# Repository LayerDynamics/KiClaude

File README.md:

# kiclaude

**Claude Code, but for circuit boards.**

kiclaude is a browser-native, AI-native, KiCad-compatible EDA suite. You open a
`.kicad_pro` project in a browser tab, chat with Claude in the sidebar, and
every action — *"add a USB-C PD trigger for 9 V, with proper decoupling and a
fuse"*, *"route the high-speed pairs first, then power"*, *"is this board ready
to fab?"* — becomes a typed tool call that round-trips back to real
`.kicad_sch` / `.kicad_pcb` files on disk. Diffable. Reviewable. Yours.

Every chat lives next to a fully-featured visual editor: selection, drag,
multi-layer routing, zone fills, DRC overlays. Claude is a first-class
collaborator, not a chrome strip glued onto someone else's UI.

---

## Why this exists

Designing a PCB today forces a hard choice:

- **KiCad** is open and file-clean, but every action is manual. AI plugins are
  second-class citizens.
- **Flux / cloud EDA** has the AI, but your files live in a vendor cloud and you
  pay rent on your own designs.
- **tscircuit** is text-first (great for AI), but you lose the visual review
  that humans actually need.

kiclaude lives in the empty quadrant: **browser-native, open file format,
AI-native, local-first.** The files stay on your disk. The AI ships in the box.
The visual editor is real. None of those are bolted on.

## What's in the box

- **A real KiCad-format engine**, in Rust + WASM — schematic parser, PCB
  parser, deterministic emitter (round-trip-or-die, gated in CI), KCIR
  canonical intermediate representation, geometry kernel, R-tree index, DRC.
- **A typed MCP tool catalog** (`kc_*` for Claude, `ui_*` for the editor) so
  every edit is auditable and gated. Claude doesn't get raw `Write` access to
  your `.kicad_pcb` — it gets `kc_footprint_place_hint("near MCU, south edge")`
  and the placer resolves it.
- **A persistent chat sidebar** powered by the Claude Agent SDK, with session
  resume, hook-gated approvals, and a journal of every tool call (with revert).
- **The same `.claude/` artifacts work everywhere.** Slash commands like
  `/add-mcu esp32-s3`, `/pcb-review`, `/diffpair`, `/route-power`, `/bom-price`,
  `/pcb-fab` run from the in-app sidebar **and** from Claude Code on the CLI.
- **Headless `kiclaude` CLI** so anything Claude can do, CI can do.
- **A three.js board viewer** (`kithree`) for the 3D crowd.
- **An optional local daemon** (`kiconnector`) so Firefox and Safari users get
  filesystem access without waiting for FSA parity.

## Eight rules we won't break

1. The **KiCad file format** is the contract. Round-trip fidelity is a CI gate.
2. The **KCIR** is the in-memory contract — Rust-defined, TS + JSON Schema
   mirrors generated from it.
3. Claude operates through **typed tools, never free-form file edits**.
4. Claude reasons in **declarative hints**; raw coordinates are UI-only.
5. **Every MPN must resolve** against a real distributor. No hallucinated parts.
6. MCP tools are **stateless**. State lives in files.
7. **No prose from MCP tools** — structured JSON only; Claude narrates on top.
8. **Local-first, cloud-optional.** Anthropic API key is the only network
   dependency, and that's opt-in at first run.

If a future PR violates one of these, that's the PR that needs to lose. Not the
rule.

## Architecture, at a squint

```
                +-------------------------------+
                |  client/  (React + Vite +     |
                |  Radix + Tailwind + Zustand)  |
                |  kicanvas + kithree viewports |
                +---------------+---------------+
                                | WebSocket + REST :8080
                +---------------v---------------+
                |  services/server  (Hono GW)   |
                +---+-----------+-----------+---+
                    |           |           |
            :8082   |   :8083   |   :8084   |
       +------------v+ +--------v---+ +-----v----------+
       |   agent     | |  kiserver  | |  kiconnector   |
       | (Claude SDK)| | (PyO3 + ki)| | (kicad-cli)    |
       +------+------+ +-----+------+ +----------------+
              |              |
              | in-process MCP (kc_* tools)
              v              v
       +------------------------------+
       |  services/mcp                |
       |  + crates/ki  (KCIR, format) |
       |  + crates/cad (geom, DRC)    |
       +------------------------------+
                       ^
                       |  round-trip
                       v
              .kicad_pro / .kicad_sch / .kicad_pcb
```

| Path | What lives there |
|---|---|
| `crates/ki/` | KCIR types, S-expression lexer/parser, KiCad 9 emitter, PyO3 + wasm bindings |
| `crates/cad/` | Geometry, R-tree index, DRC kernel, length-match, impedance solver, 3D scene |
| `services/agent/` | FastAPI driver around the Claude Agent SDK (`:8082`) |
| `services/mcp/` | In-process MCP server with all `kc_*` and `ui_*` tools |
| `services/kiserver/` | FastAPI surface around the PyO3-loaded `ki_native` (`:8083`) |
| `services/kiconnector/` | Local broker for `kicad-cli` + Freerouting (`:8084`) |
| `services/server/` | Hono WebSocket + REST gateway (`:8080`) |
| `client/` | The browser editor (React 19, Vite, Tailwind, Zustand) |
| `packages/cli/` | The `kiclaude` Node CLI |
| `packages/kithree/` | three.js board viewer |
| `examples/blinky/` | Reference project the round-trip CI runs against |

## Quick start

```bash
# Rust
cargo test --workspace
cargo clippy --workspace --all-targets -- -D warnings

# Wasm bindings (consumed by client/)
wasm-pack build --target web crates/ki
wasm-pack build --target web crates/cad

# Python services
uv sync --all-extras
uv run pytest

# Node side
pnpm install
pnpm -r typecheck
pnpm -F client dev          # browser editor on http://localhost:5173

# CLI
pnpm -F @kiclaude/cli build
kiclaude --version
kiclaude mcp stdio          # talk to the MCP server from any MCP-capable host
kiclaude validate examples/blinky
```

For end-to-end Playwright smoke (gated on `ANTHROPIC_API_KEY`):

```bash
pnpm -F e2e test
```

## A taste of the slash commands

These ship in `.claude/commands/` and work both in-app and in Claude Code:

| Command | What it does |
|---|---|
| `/add-mcu esp32-s3` | Adds an MCU + USB + LDO + decoupling, ERC-clean |
| `/add-power buck-3v3-from-vbus` | Drops in a complete power subsystem |
| `/add-decoupling` | Audits every IC for missing bypass caps, proposes one per pin |
| `/diffpair` | Declares a diff pair, solves for impedance, routes it |
| `/route-power` | Routes power nets at net-class width with per-net approvals |
| `/route-signals` | Walk-around routes signal nets in dependency order |
| `/length-match` | Analyses declared length-match groups, queues serpentine tuning |
| `/explore-placements` | Spawns a sub-agent that tries N placements, ranks by track length × clearance headroom |
| `/erc-fix` / `/drc-fix` | Reads the highest-severity issue, proposes one fix, applies on approval, loops |
| `/pcb-review` | Full M3 design review: stackup, net classes, diff pairs, length match, decoupling, DRC |
| `/pcb-fab` | DFM dry-run, then full fab bundle (gerbers + drill + P&P + BOM) |
| `/bom-price` | Fan-out across Octopart / Mouser / Digi-Key / JLCPCB, returns cheapest mix |

## Status

We're tracking the [`M0–M3` plan](docs/plans/2026-05-21-kiclaude-m0-m3.md) —
139 of 146 tasks done as of this writing. The remaining set is the push-and-shove
router (the bottleneck), three live-distributor adapters, and a couple of UI gestures.
The full spec lives at [`docs/specs/SPEC-01-kiclaude.md`](docs/specs/SPEC-01-kiclaude.md);
if it disagrees with this README, the spec wins.

## License

Apache-2.0. The Freerouting integration runs as a separately-installed
subprocess so the GPL doesn't bleed into the rest of the tree
(see `NFR-009` in the spec, and `scripts/license_audit.sh` in CI).

## Contributing

The bar:

- `cargo test --workspace` is green
- `uv run pytest` is green
- `pnpm -r typecheck && pnpm -r test` are green
- Golden round-trip (`tests/golden/`) is green — if it isn't, the file emitter
  is wrong, even if KiCad opens the output
- New MCP tools land in the typed registry with input/output schemas and a
  note on whether they're Claude-facing (declarative) or UI-only (coordinate)

Open an issue, open a PR, or — easiest of all — open the project in the
browser and ask Claude to do it.

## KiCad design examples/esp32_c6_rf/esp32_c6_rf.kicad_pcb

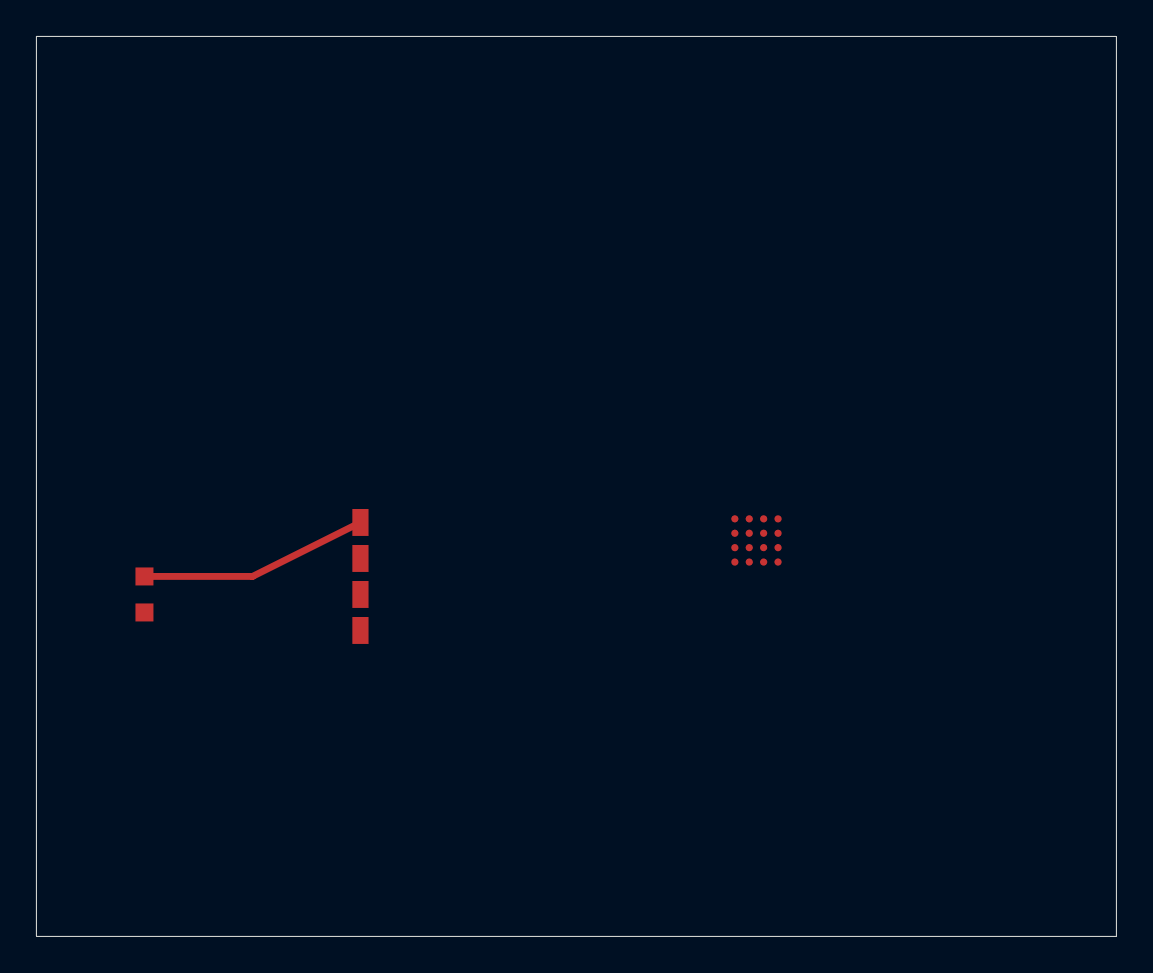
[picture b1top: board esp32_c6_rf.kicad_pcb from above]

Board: 4 copper layers, 60.0 x 50.0 mm, 7 parts (0 on the bottom side), 2 nets.

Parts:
C1, C2: 100nF; C_0402_1005Metric
C3, C4: 4.7uF; C_0402_1005Metric
J1: U.FL; U.FL_Molex_MCRF_73412-0110_Vertical
U1: ESP32-C6-MINI-1
U2: BGA-16; BGA-16_1.92x1.92mm_Layout4x4_P0.5mm

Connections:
+1V35: U2.A2, U2.A4
GND: J1.2, U1.2, U2.A1, U2.A3, U2.B2, U2.B4, U2.C2, U2.C4
